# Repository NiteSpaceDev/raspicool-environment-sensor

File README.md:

# Environment sensor module based on the ESP32-Wroom Module

## Overview

This environment sensor is intended to be a low cost sensor that can be deployed throughout the environment controlled by the RaspiCool system.

## Recommended sensor locations
* One sensor for each room
  * Thermostat includes a sensor and only needs a sensor module if drafts, etc. make the built-in sensor unreliable.
* One sensor for each return air vent
* One sensor in the vent closest to the AC coil
  * This sensor, combined with the return air sensors, is used to track 'delta-t', which can help indicate system troubles.

## Hardware description
The sensor module is built using an esp32-wroom module, providing encryption, wifi, and bluetooth capabilities.  The primary sensor included is the BME280, providing temperature, humidity, and pressure data.   Power is provided by an 18650 battery.

## Sensor Options
* Option to include SSD1306 oled display
* SPI and I2C expansion points included on sensor pcb

# Usage
## Sensor pairing
The base sensor image does not include any wifi configuration or authentication certificates.   When the sensor is powered in this state, it will scan bluetooth looking for a RaspiCool thermostat.   When it finds one, it will trigger a popup on the thermostat to confirm pairing the sensor.

* Note:   The thermostat must be set into pairing mode in order to pair additional sensors.  Bluetooth is normally off on the thermostat.

Pairing causes the following events:
- Wifi configuration is sent via bluetooth to the sensor
- Thermostat will assign a static IP and set a static DHCP reservation for the sensor
- Sensor receives IP via DHCP and verifies the address with the thermostat registration service
- Client authentication certificates are generated and delivered to the sensor
- Sensor retrieves additional configuration from the thermostat services
- Sensor resets and starts normal data loop

## Sensor operation
In normal operation, the sensor spends the majority of the time in a sleep state.  During each wake cycle, the following events happen:
* Read sensor values
* Cache current value
* Determine if values need to be reported - Enter sleep at this point if no reporting needed
  * Sensor values have changed by more than threshhold (Default 0.1c, 0.5%) 
  * Reporting cycle time has expired (Default 1 minute)
* Bring wifi online
* Connect to thermostat
* Send sensor data
* Check for commands (Update, config, etc.)
* Enter sleep

TODO:   Thermostat data via https api instead of mqtt?

## How to install this app

- mos build
- mos flash

## Helpful commands
- See bashaliases.sh for information

# Built for (MongooseOS)[https://mongoose-os.com]

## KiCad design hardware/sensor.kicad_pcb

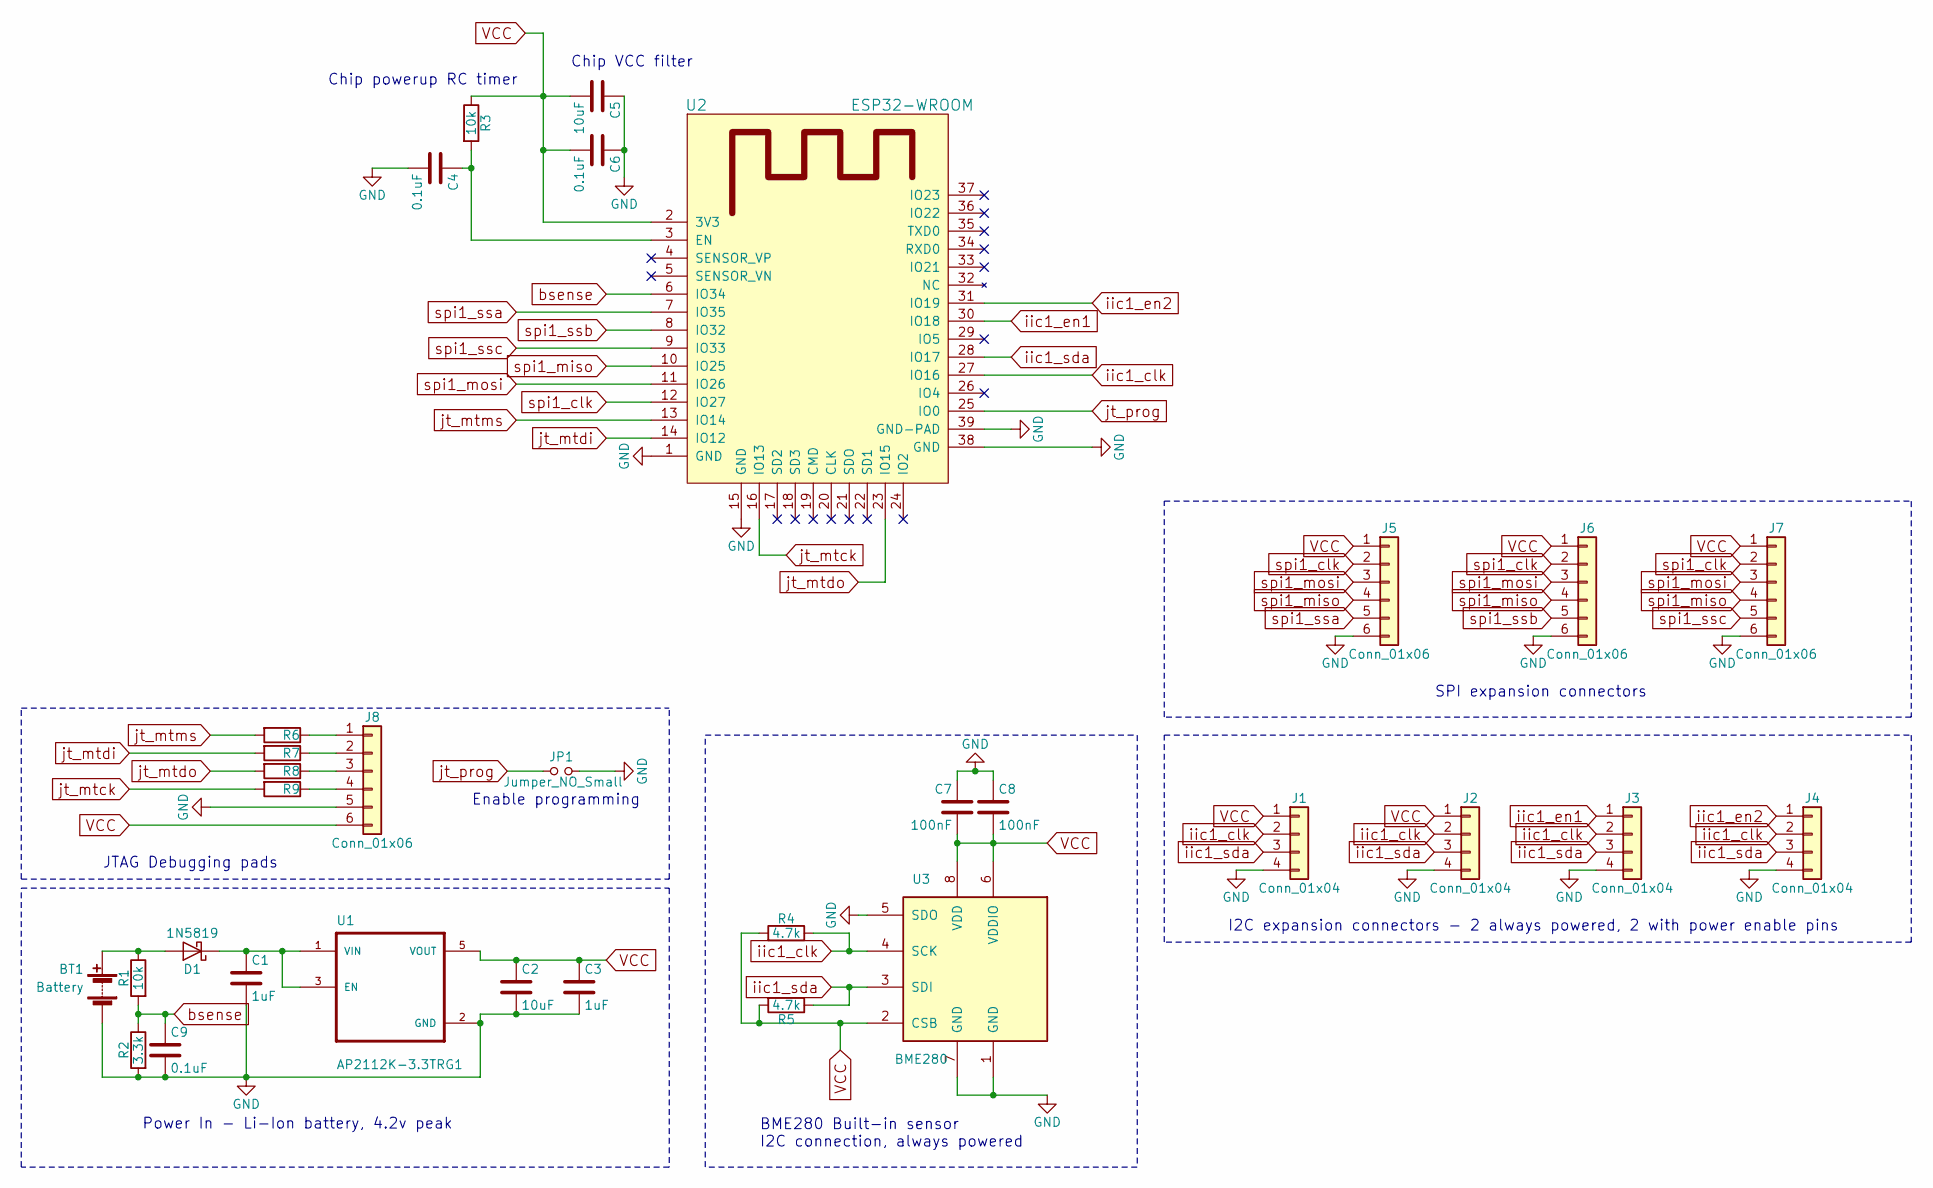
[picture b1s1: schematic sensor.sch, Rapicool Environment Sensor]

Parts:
BT1: Battery; Keystone_1042_1x18650
C1, C3: 1uF; C_1206
C2, C5: 10uF; C_1206
C4, C6, C9: 0.1uF; C_1206
C7, C8: 100nF; C_1206
D1: 1N5819; D_1206
J1, J2, J3, J4: Conn_01x04; Pin_Header_Straight_1x04_Pitch2.54mm
J5, J6, J7, J8: Conn_01x06; Pin_Header_Straight_1x06_Pitch2.54mm
JP1: Jumper_NO_Small; Pin_Header_Straight_1x02_Pitch2.54mm
R1, R3: 10k; R_1206
R2: 3.3k; R_1206
R4, R5: 4.7k; R_1206
R6, R7, R8, R9: 100; R_1206
U1: AP2112K-3.3TRG1; SOT95P285X140-5N
U2: ESP32-WROOM
U3: BME280; Bosch_LGA-8_2.5x2.5mm_Pitch0.65mm_ClockwisePinNumbering

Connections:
GND: BT1.2 (-), C1.2, C2.2, C3.2, C4.2, C5.1, C6.1, C7.1, C8.1, C9.2, J1.4, J2.4, J3.4, J4.4, J5.6, J6.6, J7.6, J8.5, JP1.2, R2.2, U1.2 (GND), U2.1 (GND), U2.15 (GND), U2.38 (GND), U2.39 (GND-PAD), U3.1 (GND), U3.5 (SDO), U3.7 (GND)
unnamed: BT1.1 (+), D1.2 (A), R1.1
unnamed: C1.1, D1.1 (K), U1.1 (VIN), U1.3 (EN)
unnamed: C4.1, R3.2, U2.3 (EN)
unnamed: J8.1, R6.1
unnamed: J8.2, R7.1
unnamed: J8.3, R8.1
unnamed: J8.4, R9.1
VCC: C2.1, C3.1, C5.2, C6.2, C7.2, C8.2, J1.1, J2.1, J5.1, J6.1, J7.1, J8.6, R3.1, R4.2, R5.2, U1.5 (VOUT), U2.2 (3V3), U3.2 (CSB), U3.6 (VDDIO), U3.8 (VDD)
bsense: C9.1, R1.2, R2.1, U2.6 (IO34)
iic1_clk: J1.2, J2.2, J3.2, J4.2, R4.1, U2.27 (IO16), U3.4 (SCK)
iic1_en1: J3.1, U2.30 (IO18)
iic1_en2: J4.1, U2.31 (IO19)
iic1_sda: J1.3, J2.3, J3.3, J4.3, R5.1, U2.28 (IO17), U3.3 (SDI)
jt_mtck: R9.2, U2.16 (IO13)
jt_mtdi: R7.2, U2.14 (IO12)
jt_mtdo: R8.2, U2.23 (IO15)
jt_mtms: R6.2, U2.13 (IO14)
jt_prog: JP1.1, U2.25 (IO0)
spi1_clk: J5.2, J6.2, J7.2, U2.12 (IO27)
spi1_miso: J5.4, J6.4, J7.4, U2.10 (IO25)
spi1_mosi: J5.3, J6.3, J7.3, U2.11 (IO26)
spi1_ssa: J5.5, U2.7 (IO35)
spi1_ssb: J6.5, U2.8 (IO32)
spi1_ssc: J7.5, U2.9 (IO33)

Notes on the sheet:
Power In - Li-Ion battery, 4.2v peak
BME280 Built-in sensor I2C connection, always powered
I2C expansion connectors - 2 always powered, 2 with power enable pins
SPI expansion connectors
Enable programming
JTAG Debugging pads
Chip VCC filter
Chip powerup RC timer

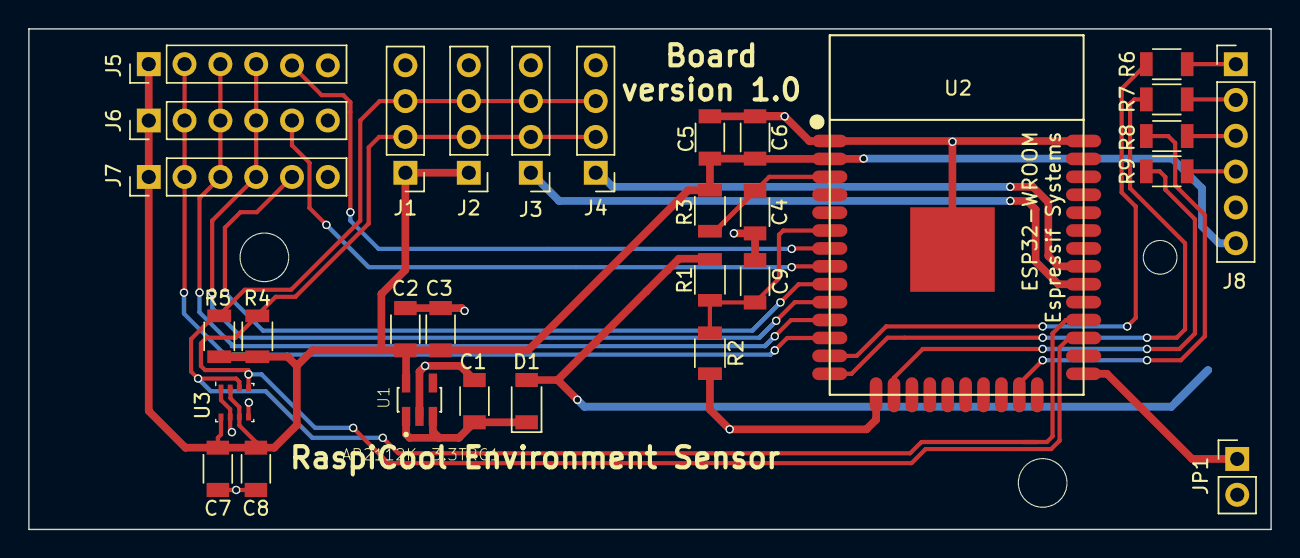
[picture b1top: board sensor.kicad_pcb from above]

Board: 2 copper layers, 88.1 x 35.5 mm, 32 parts (1 on the bottom side), 25 nets.

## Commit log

2018-05-21 Ignore build and deps tree
2018-05-21 First round of code to test
    Testing out code based on the advanced-javascript example.
2018-05-21 Add Humidity call
    Fix default pin to IO-5
2018-05-21 Make an app setting for the sensor type too
2018-05-21 Add F to the console output
2018-05-21 Output update, setup Local OTA updates
    Change console output to have both temp & humidity on the same line
    Add HTTP server OTA updates option for devel purposes
2018-05-22 Rough OLED support - output temp only
    Rough testing version, not yet verified working
2018-05-22 Use GPIO pin 2 by default
    This will get sorted out in a stable fashion once the design is taken off breadboard and put to hardware.
2018-05-24 Ignore cert files
    no mucking about with certs in the repo
2018-05-24 Working super basic version of OLED support
    This has a ton of cleanup still needed, but it does bring the OLED online for the new ESP32 board being tested
    Next up is some additional testing to confirm if we actually need pin16 high and a ton of cleanup. Part of the cleanup should include sticking the OLED code into different modules and choosing what w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
    Note - The code base will be targeted towards specific hardware configs, but we want to keep some open source flexibility in the design
2018-05-26 Working BME280 sensor code
    BME 280 sensor working except for humidity, Code cleanup and refactor due next.
2018-05-27 Add some handy build / update commands
2018-05-27 Some minor cleanups, extend display code
    Display is updated to output temp in both C & F, plus pressure & humidity
2018-05-30 Build command aliases
2018-05-30 Restructure sensor data collection
    Collect sensor data directly into JSON data structure. Slow collection pace, start attempting to collect battery data. Publish sensor data to MQTT.
2018-06-09 Pass IP on alias commandline
2018-06-09 Some of the SSD1306 calls seem to have changed
    Fixup some of the FFI prototypes
2018-06-09 Updates to MQTT pushes
    * Start building deeper application config
    * Pull sensor name from config
    * Continue attempts to get usable data from ADC
2018-06-25 Start describing bus usage
2018-06-26 Add I2C info on BME280 sensor
2018-07-01 mosbuild function will always build esp32
2018-07-01 Start building hardware schematics
    Building in KiCad
2018-07-02 Continue schematic work
    Cleanup power
    Add I2C connectors
    Connect BME280 w/ I2C
2018-07-02 Err.. backups shouldn't have been committed
2018-07-03 Continue HW design
    * Setup SPI expansion connectors
    * Re-annotate caps for power regulator and WROOM power
    * Add globals for JTAG pins
    * Rough grouping of parts on PCB
    - Note - still need to make battery setup choices and footprint choices for passives
2018-07-03 Hierarchy doesn't make sense
    This is already gone from the schematic - hierarchy doesn't make sense for this module
2018-07-04 Sensor board v1 schematic done
    * JTAG added
    * Keep latest schematic in PDF for easy viewing
    * Attempt to fix markdown on hardware description
2018-07-04 Additional tweaks
    Update footprints for SPI & I2C expansion
    Set resistor values for battery voltage divider
    Series resistors for JTAG
2018-07-05 Additional fixes, Place & route board
    * Add junction on C9 to GND
    * Swap SPI pins for cleaner routing
    * Finish initial routing of board
    TODO: Finish silkscreen layout
    * Reference labels
    * Page labels
2018-07-05 V1.0 board done
    * Refs updated
    * version info added
    Note - For now, we're leaving the gerber output directory out of the github project
    Sensor.csv is early BOM
    TODO:
    * Update hardware markdown with new pin info, including board references
2018-07-07 Update hardware description
    * Add BOM
    * Update pin assignments for SPI
    * Add description for SPI / I2C expansion headers
    * Remove esp8266 config
2018-07-10 Describe sensor design
2018-07-29 Hardware V1 code functional
    Some minor migrations to get this code functional with the V1 sensor hardware config. Test build w/ programmer and breadboard with hardware pinout.
2018-10-12 Build a docker container to run builds in
    Borrow and extend Docker tools from https://github.com/bschwind/esp-32-build
    Add items to install PIP + toolchain required packages
    docker-compose config untested
    TODO:
    * Build makefile with targets for docker container & running docker
    environment
2018-10-15 Shift Docker build elements to separate repo as submodule
